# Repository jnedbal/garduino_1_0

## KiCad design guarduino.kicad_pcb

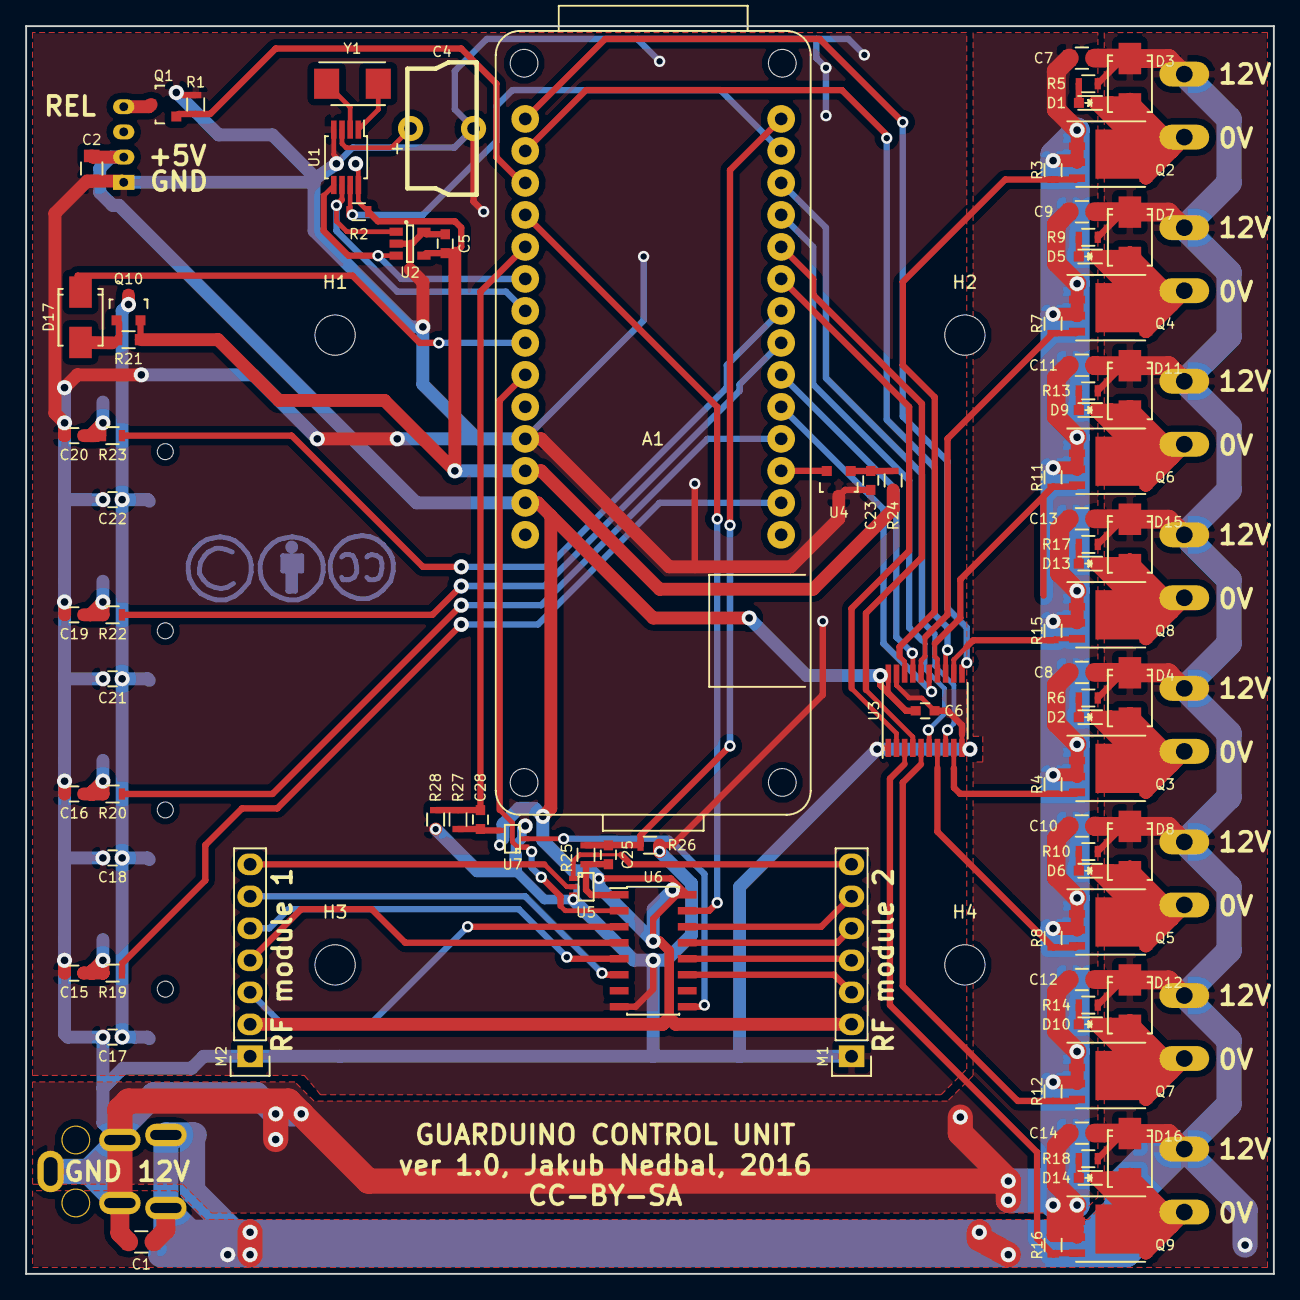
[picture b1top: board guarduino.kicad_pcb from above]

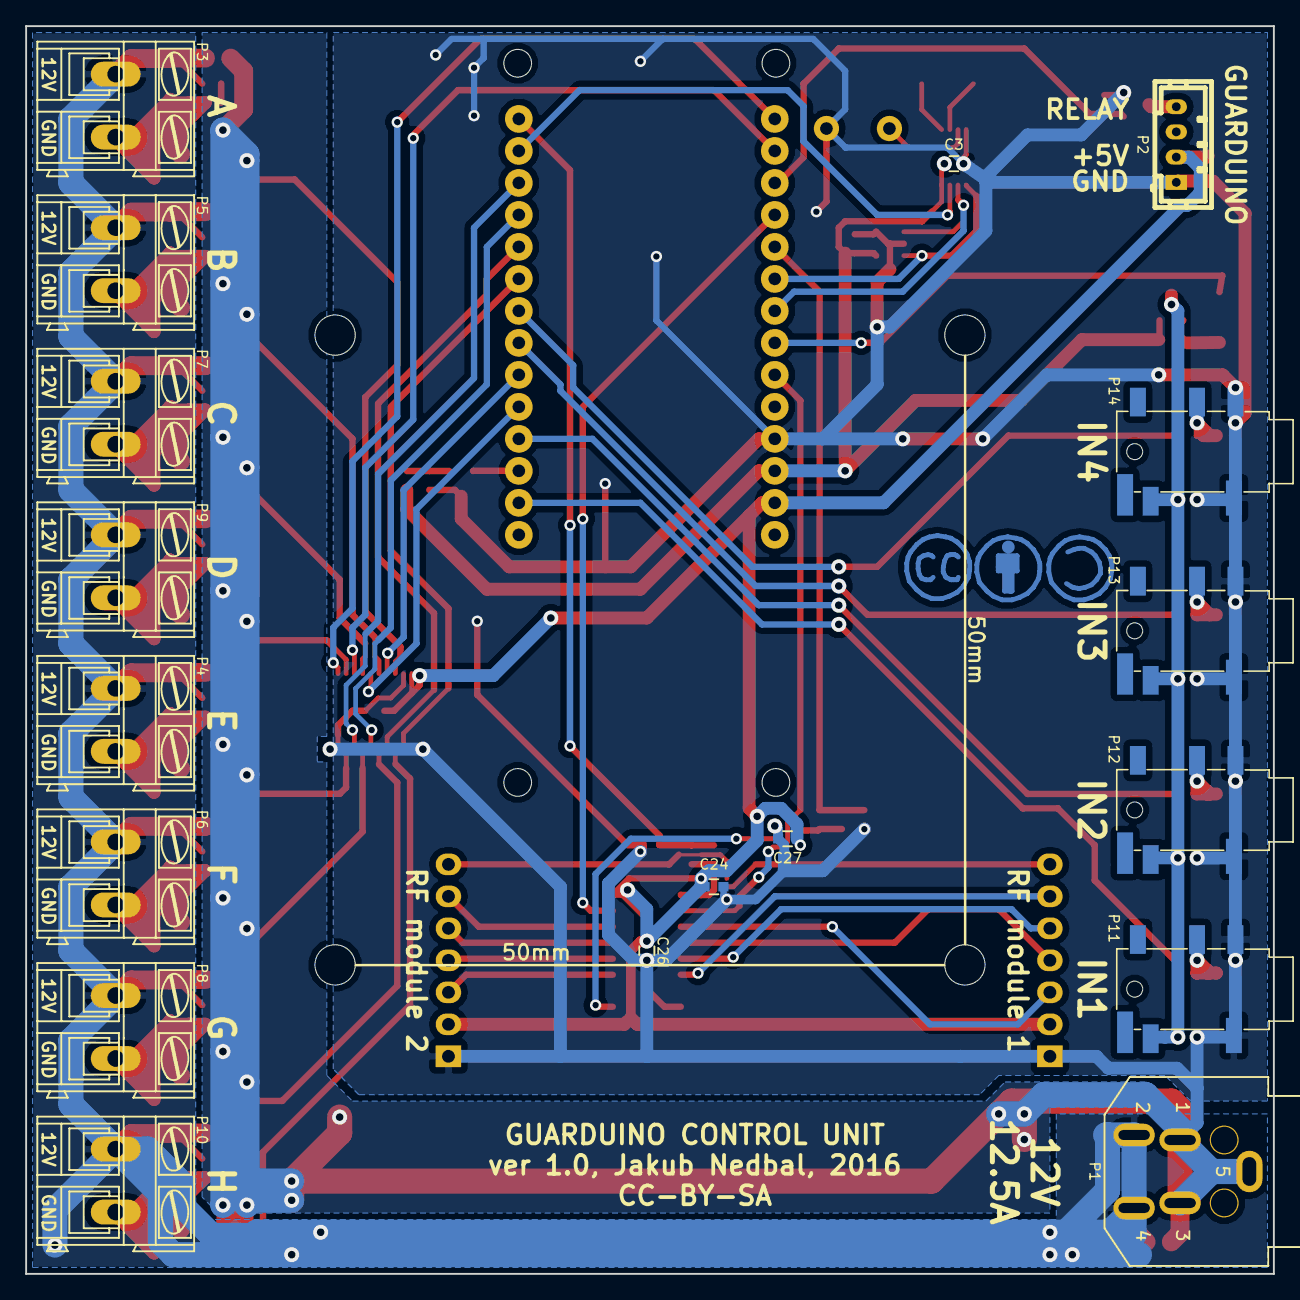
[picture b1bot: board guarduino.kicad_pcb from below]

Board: 2 copper layers, 99.1 x 99.1 mm, 112 parts (18 on the bottom side), 74 nets.

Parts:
A1: ARDUINO_MKR1000
C1, C2, C7, C8, C9, C10, C11, C12, C13, C14: 10u/25V; C_0805
C3, C5, C6, C15, C16, C17, C18, C19, C20, C21, C22, C24, C26, C27: 100n; C_0603
C4: 0.33F/5.5V; SD_CAP
C23: 1u; C_0603
C25, C28: 10p; C_0603
D1, D2, D5, D6, D9, D10, D13, D14: LED GREEN; LED_0603
D3, D4, D7, D8, D11, D12, D15, D16, D17: 1N5819; SMA_Standard
H1, H2, H3, H4: ⌀3mm; MountingHole_3.2mm_M3
M1, M2: PT2272; Socket_Strip_Straight_1x07
P1: 4way mini DIN; MiniDIN4way
P2: 4way connector; JST_PH_04way_vert
P3, P4, P5, P6, P7, P8, P9, P10: GS009S; AK300-2
P11, P12, P13, P14: 3pin 3.5mm jack; SUNTECH_ST-PJ-312
Q1: CJ2302; SOT-23
Q2, Q3, Q4, Q5, Q6, Q7, Q8, Q9: PSMN6R0; SO-8_PowerPAK_Vishay_Single
Q10: FDN340P; SOT-23
R1, R3, R4, R7, R8, R11, R12, R15, R16, R21: 560k; R_0603
R2, R5, R6, R9, R10, R13, R14, R17, R18: 10k; R_0603
R19, R20, R22, R23, R25, R27: 1k5; R_0603
R24: 220R; R_0603
R26, R28: 3k; R_0603
U1: DS1339; MSOP-8_3x3mm_Pitch0.65mm
U2: 24AA16T; SOT-23-5
U3: 74AHCT244; TSSOP-20_4.4x6.5mm_Pitch0.65mm
U4: MCP9700; SOT-23
U5: 74AHC1G02; SC-70-5
U6: 74HCT165; SOIC-16_3.9x9.9mm_Pitch1.27mm
U7: 74AHCT1G125; SC-70-5
Y1: 32.768kHz; Crystal_SMD_5032_2Pads

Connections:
+3V3: A1.26, C3.1, C5.1, Q10.2, R2.1, R21.1, R24.1, U1.8, U2.4
+12V: C1.1, C7.1, C8.1, C9.1, C10.1, C11.1, C12.1, C13.1, C14.1, D3.1, D4.1, D7.1, D8.1, D11.1, D12.1, D15.1, D16.1, P1.1, P1.2, P3.1, P4.1, P5.1, P6.1, P7.1, P8.1, P9.1, P10.1, R5.1, R6.1, R9.1, R10.1, R13.1, R14.1, R17.1, R18.1
/POWER: A1.17, Q1.1, R1.1
/PowerDrivers/D0: A1.9, U3.2
/PowerDrivers/D1: A1.10, U3.4
/PowerDrivers/D2: A1.11, U3.6
/PowerDrivers/D3: A1.12, U3.8
/PowerDrivers/D4: A1.15, U3.11
/PowerDrivers/D5: A1.16, U3.13
/PowerDrivers/D6: A1.5, U3.15
/PowerDrivers/D7: A1.6, U3.17
/PowerDrivers/OUT0: Q2.4, R3.1, U3.18
/PowerDrivers/OUT1: Q4.4, R7.1, U3.16
/PowerDrivers/OUT2: Q6.4, R11.1, U3.14
/PowerDrivers/OUT3: Q8.4, R15.1, U3.12
/PowerDrivers/OUT4: Q3.4, R4.1, U3.9
/PowerDrivers/OUT5: Q5.4, R8.1, U3.7
/PowerDrivers/OUT6: Q7.4, R12.1, U3.5
/PowerDrivers/OUT7: Q9.4, R16.1, U3.3
/RELAY: P2.4, Q1.3
/RFmodules/D0_1: M1.3, U6.11
/RFmodules/D0_2: M2.3, U6.3
/RFmodules/D1_1: M1.4, U6.12
/RFmodules/D1_2: M2.4, U6.4
/RFmodules/D2_1: M1.5, U6.13
/RFmodules/D2_2: M2.5, U6.5
/RFmodules/D3_1: M1.6, U6.14
/RFmodules/D3_2: M2.6, U6.6
/RFmodules/MISO: A1.19, C28.1, R27.1, R28.1
/RFmodules/RF_DATA: C25.2, R25.2, U5.4, U6.1
/RFmodules/RF_DATA_3V3: A1.14, C25.1, R25.1, R26.1
/RFmodules/SCK: A1.18, U6.15
/RFmodules/SD1: U6.9, U7.2
/RFmodules/SD2: C28.2, R27.2, U7.4
/RFmodules/VT_1: M1.7, U5.1
/RFmodules/VT_2: M2.7, U5.2
/RFmodules/~CS_RF: A1.23, U6.2, U7.1
/SCL: A1.21, U1.6, U2.1
/SDA: A1.20, U1.5, U2.3
/Sensors/SENS0: A1.2, R19.2
/Sensors/SENS1: A1.4, R20.2
/Sensors/SENS2: A1.7, R22.2
/Sensors/SENS3: A1.8, R23.2
/Sensors/TEMP: A1.3, U4.2
/Sensors/~SENS: A1.22, D17.1
/~RTC_INT: A1.13, R2.2, U1.7
GND: A1.25, C1.2, C2.2, C3.2, C4.2, C5.2, C6.2, C7.2, C8.2, C9.2, C10.2, C11.2, C12.2, C13.2, C14.2, C15.2, C16.2, C17.2, C18.2, C19.2, C20.2, C21.2, C22.2, C23.2, C24.2, C26.2, C27.2, M1.1, M2.1, P1.3, P1.4, P1.5, P2.1, P11.COM1, P11.COM2, P12.COM1, P12.COM2, P13.COM1, P13.COM2, P14.COM1, P14.COM2, Q1.2, Q2.1, Q2.2, Q2.3, Q3.1, Q3.2, Q3.3, Q4.1, Q4.2, Q4.3, Q5.1, Q5.2, Q5.3, Q6.1, Q6.2, Q6.3, Q7.1, Q7.2, Q7.3, Q8.1, Q8.2, Q8.3, Q9.1, Q9.2, Q9.3, R1.2, R3.2, R4.2, R7.2, R8.2, R11.2, R12.2, R15.2, R16.2, R26.2, R28.2, U1.4, U2.2, U2.5, U3.1, U3.10, U3.19, U4.3, U5.3, U6.8, U7.3
unnamed: C4.1, U1.3
unnamed: C15.1, P11.R, R19.1
unnamed: C16.1, P12.R, R20.1
unnamed: C17.1, C18.1, C21.1, C22.1, P11.L, P12.L, P13.L, P14.L, Q10.3
unnamed: C19.1, P13.R, R22.1
unnamed: C20.1, P14.R, R23.1
unnamed: C23.1, R24.2, U4.1
unnamed: D1.1, D3.2, P3.2, Q2.5
unnamed: D1.2, R5.2
unnamed: D2.1, D4.2, P4.2, Q3.5
unnamed: D2.2, R6.2
unnamed: D5.1, D7.2, P5.2, Q4.5
unnamed: D5.2, R9.2
unnamed: D6.1, D8.2, P6.2, Q5.5
unnamed: D6.2, R10.2
unnamed: D9.2, R13.2
unnamed: D10.1, D12.2, P8.2, Q7.5
unnamed: D10.2, R14.2
unnamed: D9.1, D11.2, P7.2, Q6.5
unnamed: D13.1, D15.2, P9.2, Q8.5
unnamed: D13.2, R17.2
unnamed: D14.1, D16.2, P10.2, Q9.5
unnamed: D14.2, R18.2
unnamed: D17.2, Q10.1, R21.2
unnamed: U1.1, Y1.2
unnamed: U1.2, Y1.1
VCC: A1.27, C2.1, C6.1, C24.1, C26.1, C27.1, M1.2, M2.2, P2.2, U3.20, U5.5, U6.16, U7.5

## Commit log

2016-06-22 Finished schematics
2016-06-26 Laid out parts and routed some of the signals
2016-10-07 Final production board
2016-10-07 Fixed order codes
2016-11-27 Flipped C6 onto the bottom layer so it doesn't clash with U3
2016-11-27 Fixed .gitignore to ignore zip files

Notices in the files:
guarduino.kicad_pcb:
License: CC-BY-SA
CC-BY-SA
